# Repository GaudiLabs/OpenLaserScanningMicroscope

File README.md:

## OpenLaserScanningMicroscope 

Open Source Laser Scanning Microscope (OpenLSM)

### Don't click on the files!
Click on the "Download ZIP" Button to the right.
Then unpack the archive.

### Open Source Digital Microfluidics Bio Lab

OpenLSM is an open source design to build a laser scanning microscope from a DVD or Blue-Ray disc reading head. 

For more info on the open source project see:
http://www.gaudi.ch/GaudiLabs/?page_id=652

### License

OpenLSM, all design files and software are licensed under a GNU GENERAL PUBLIC LICENSE
See license file in the repository.

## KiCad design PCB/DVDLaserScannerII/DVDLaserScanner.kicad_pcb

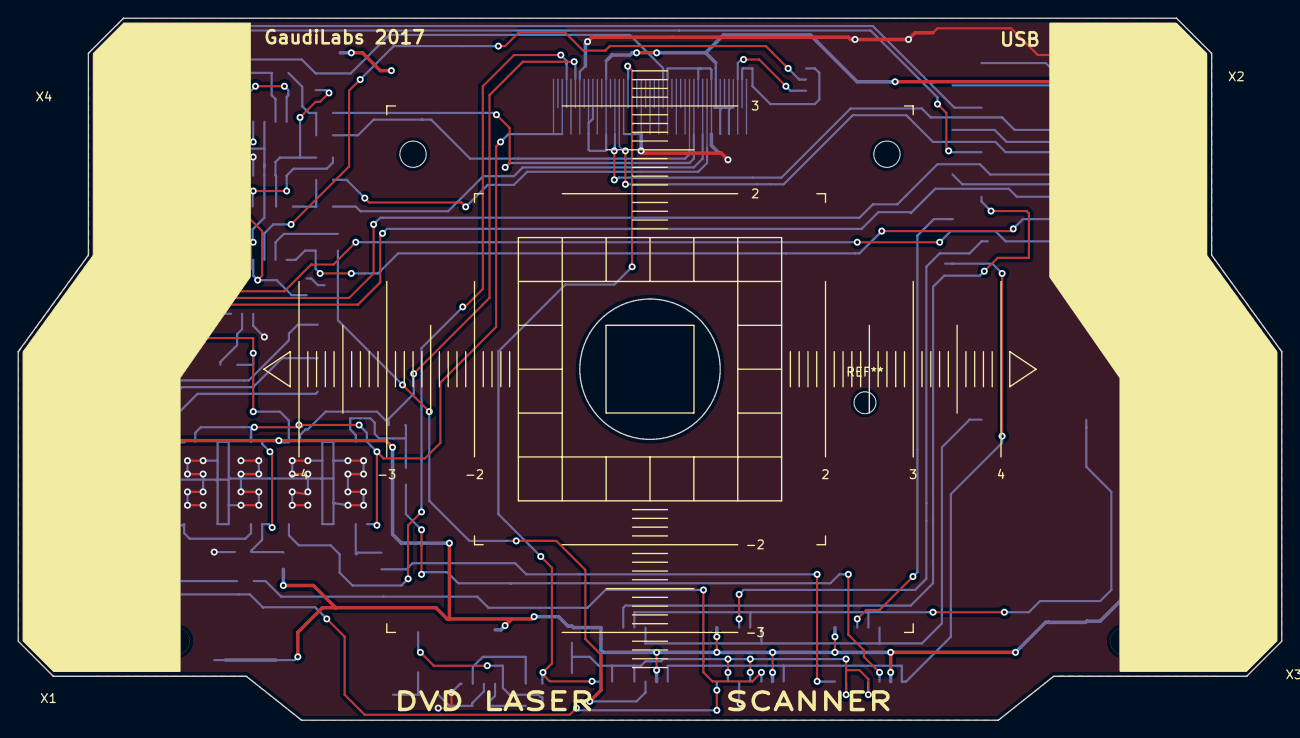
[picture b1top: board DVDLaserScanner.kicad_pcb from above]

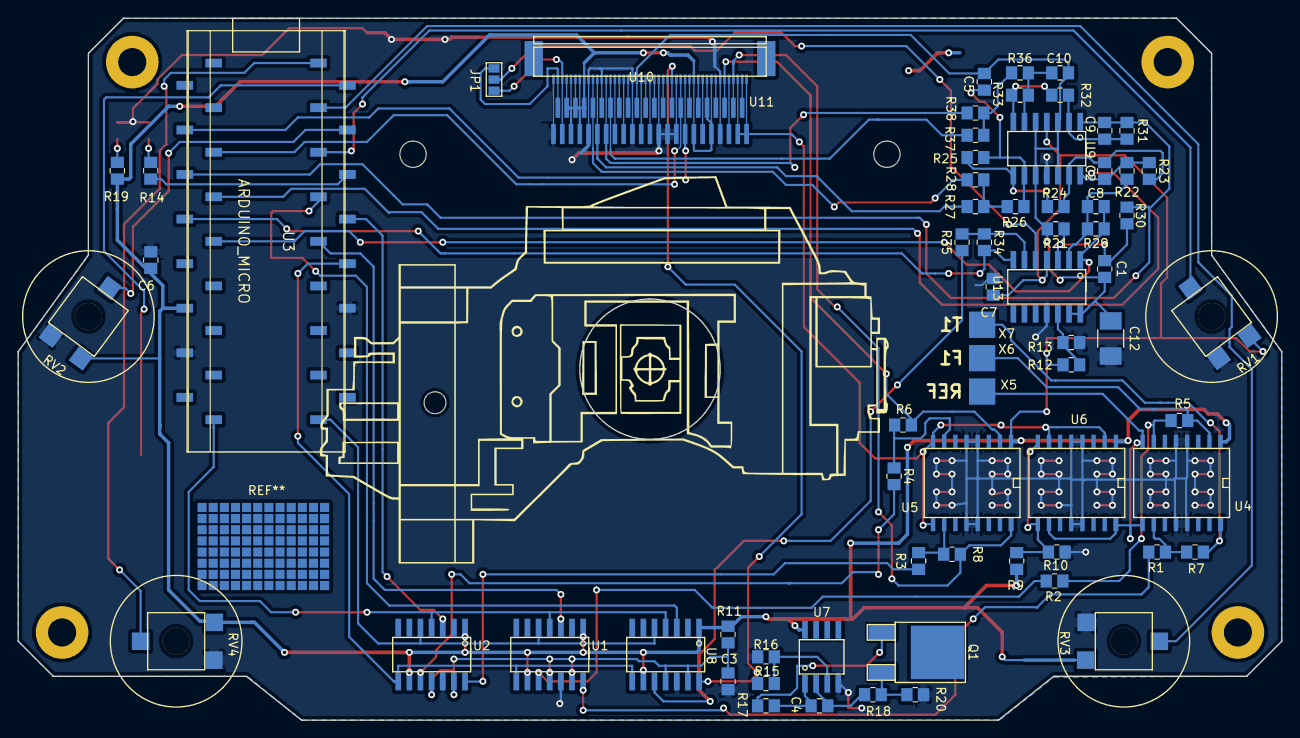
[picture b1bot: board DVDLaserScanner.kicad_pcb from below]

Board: 2 copper layers, 144.0 x 80.0 mm, 77 parts (70 on the bottom side), 80 nets.

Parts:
C1, C8: 22pF; 0805G
C2, C9: 39pF; 0805G
C3: 100nF; 0805G
C4, C6, C7: 100n; 0805G
C5, C10: 10pF; 0805G
C12: 100nF; C_1210_HandSoldering
D1, D2: LED; 0805G
JP1: Jumper_NC_Dual; GS3
Q1: Q_NMOS_GDS; TO-252-2Lead
R1, R3, R5, R6: 15k; 0805G
R2, R4: 270k; 0805G
R7, R8, R15: 8.2k; 0805G
R9, R10, R12: 4.7k; 0805G
R11: 100k; 0805G
R13: 3.3k; 0805G
R14, R19: 470; 0805G
R16: 1.8k; 0805G
R17: 100; 0805G
R18, R22, R30: 10k; 0805G
R20: 10; 0805G
R21, R29: 39k; 0805G
R23, R31: 180k; 0805G
R24, R32: 68k; 0805G
R25, R33: 18k; 0805G
R26, R36: 56k; 0805G
R27, R28, R37, R38: 1.2k; 0805G
R34: 560k; 0805G
R35: 2.7k; 0805G
RV1, RV2, RV3, RV4: POT; CA6_VSMD
SW1: BUT; PUSH_BUTTON_SMD
U1, U2, U8: MCP4922-E/SL; SOIC-14_N
U3: ARDUINO_MICRO; ARDUINO_MICRO_SMD
U4, U5, U6: TCA0372_DWG; SO-16-W
U7: MCP6002; SOIC-08_N
U9, U13: TLC2274; SOIC-14_N
U10: Con45; Pads
U11: Con45; FFC_05_45
X1, X2, X3, X4: MountPad3; MountingHoleM3
X5, X6, X7: PAD; PAD_SMD_3mm

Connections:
A_SIG: R37.1, U10.32, U11.32
B_SIG: R27.1, U10.35, U11.35
C_SIG: R38.1, U10.33, U11.33
DAC1CS: U1.3, U3.9
DAC2CS: U2.3, U3.10
DAC3CS: U3.11, U8.3
DAC_DI: U1.5, U2.5, U3.1, U8.5
DAC_LATCH: U1.8, U2.8, U3.8, U8.8
DAC_SCK: U1.4, U2.4, U3.34, U8.4
D_SIG: R28.1, U10.36, U11.36
F1+: R5.1, U4.2, X6.1
F2+: R8.1, U5.16, U10.4, U11.4
F-: U5.8, U5.9, U6.2, U6.7, U10.1, U10.3, U11.1, U11.3
GND: C3.2, C6.2, C7.2, C12.2, D1.1, D2.1, R10.2, R13.1, R16.2, R20.1, RV1.3, RV2.3, RV3.3, RV4.3, SW1.2, U1.12, U2.12, U3.6, U3.31, U4.4, U4.5, U4.12, U4.13, U5.4, U5.5, U5.12, U5.13, U6.4, U6.5, U6.12, U6.13, U7.4, U8.12, U9.11, U10.7, U10.17, U10.19, U10.21, U10.27, U10.34, U10.37, U10.45, U11.7, U11.17, U11.19, U11.21, U11.27, U11.34, U11.37, U11.45, U13.11
INTENSITY: R15.1, U8.14, U10.18, U11.18
unnamed: C1.2, R21.2, R30.2, U13.3
unnamed: C2.1, R23.1, R24.2, U9.13
unnamed: C4.1, R17.2, U7.1
unnamed: C4.2, R18.2, U7.2
unnamed: C5.1, R25.1, R26.2, U9.9
unnamed: C8.2, R22.2, R29.2, U13.2
unnamed: C9.1, R31.1, R32.2, U9.2
unnamed: C10.1, R33.1, R36.2, U9.6
unnamed: D1.2, R14.2
unnamed: D2.2, R19.2
unnamed: JP1.2, U13.5
unnamed: Q1.1, R17.1
unnamed: Q1.3, R18.1, R20.2
unnamed: R1.1, R7.2, U4.10
unnamed: R1.2, U1.14
unnamed: R2.1, R5.2, U4.7
unnamed: R2.2, U1.10
unnamed: R3.1, R8.2, U5.10
unnamed: R3.2, U2.14
unnamed: R4.1, R6.2, U5.7
unnamed: R4.2, U2.10
unnamed: R9.2, R10.1, U6.8, U6.9
unnamed: R12.1, R13.2, U13.12
unnamed: R14.1, U3.12
unnamed: R15.2, R16.1, U7.3
unnamed: R24.1, R25.2, U9.8
unnamed: R26.1, R27.2, R28.2
unnamed: R32.1, R33.2, U9.7
unnamed: R34.2, R35.1, U13.6
unnamed: R36.1, R37.2, R38.2
unnamed: SW1.1, U3.16
unnamed: U10.2, U11.2
unnamed: U10.5, U11.5
unnamed: U10.8, U11.8
unnamed: U10.11, U11.11
unnamed: U10.12, U11.12
unnamed: U10.14, U11.14
unnamed: U10.20, U11.20
unnamed: U10.22, U11.22
unnamed: U10.23, U11.23
unnamed: U10.24, U11.24
unnamed: U10.25, U11.25
unnamed: U10.28, U11.28
unnamed: U10.29, U11.29
unnamed: U10.30, U11.30
unnamed: U10.31, U11.31
OFFSET: R35.2, U8.10
PD_AC: C9.2, R30.1, R31.2, U3.23, U9.1
PD_BD: C2.2, R22.1, R23.2, U3.24, U9.14
PD_FE: C8.1, R29.1, U3.26, U13.1
PD_RF: R34.1, U3.25, U13.7
POT1: RV1.2, U3.13
POT2: RV2.2, U3.14
POT3: RV3.2, U3.15
POT4: RV4.2, U3.17
RF1: JP1.1, U10.43, U11.43
RF2: JP1.3, U10.44, U11.44
SEL1: U3.22, U10.16, U11.16
SEL2: U3.21, U10.15, U11.15
T1+: R7.1, U4.16, X7.1
T2+: R6.1, U5.2, U10.6, U11.6
VCC_BLUE: C6.1, C7.1, R9.1, R11.1, R12.2, R19.1, RV1.1, RV2.1, RV3.1, RV4.1, U1.1, U1.9, U2.1, U2.9, U3.29, U4.1, U5.1, U6.1, U7.8, U8.1, U8.9, U9.4, U10.9, U10.10, U10.13, U10.38, U10.39, U10.40, U10.41, U10.42, U11.9, U11.10, U11.13, U11.38, U11.39, U11.40, U11.41, U11.42, U13.4
VREF: C1.1, C5.2, C10.2, C12.1, R21.1, U9.3, U9.5, U9.10, U9.12, U10.26, U11.26, U13.13, U13.14
VREF1: U4.8, U4.9, U6.10, U6.16, X5.1
VREF_DAC: C3.1, R11.2, U1.11, U1.13, U2.11, U2.13, U8.11, U8.13

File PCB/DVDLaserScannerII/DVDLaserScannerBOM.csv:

"Id";"Designator";"Package";"Quantity";"Designation";"Supplier and ref";
1;"REF**";"MicroscopeyScale";1;"MicroscopeyScale";;;
2;"U11";"FFC_05_45";1;"Con45";;;
3;"RV4,RV3,RV2,RV1";"CA6_VSMD";4;"POT";;;
4;"U1,U2,U8";"SOIC-14_N";3;"MCP4922-E/SL";;;
5;"U3";"ARDUINO_MICRO_SMD";1;"ARDUINO_MICRO";;;
6;"X1,X2,X3,X4";"MountingHoleM3";4;"MountPad3";;;
7;"C3";"0805G";1;"100nF";;;
8;"R1,R3,R5,R6";"0805G";4;"15k";;;
9;"R2,R4,R26,R36";"0805G";4;"56k";;;
10;"R7,R8,R15";"0805G";3;"8.2k";;;
11;"R9,R10,R12,R34,R35";"0805G";5;"4.7k";;;
12;"R11";"0805G";1;"100k";;;
13;"R13";"0805G";1;"3.3k";;;
14;"C4,C6,C7";"0805G";3;"100n";;;
15;"D1,D2";"0805G";2;"LED";;;
16;"Q1";"TO-252-2Lead";1;"Q_NMOS_GDS";;;
17;"R14,R19";"0805G";2;"470";;;
18;"R16";"0805G";1;"1.8k";;;
19;"R17";"0805G";1;"100";;;
20;"R18,R22,R30";"0805G";3;"10k";;;
21;"R20";"0805G";1;"10";;;
22;"U7";"SOIC-08_N";1;"MCP6002";;;
23;"REF**,REF**";"MountingHole_3mm";2;"MountingHole_3mm";;;
24;"JP1";"GS3";1;"Jumper_NC_Dual";;;
25;"R21,R29";"0805G";2;"39k";;;
26;"U4,U5,U6";"SO-16-W";3;"TCA0372_DWG";;;
27;"U10";"Pads";1;"Con45";;;
28;"SW1";"PUSH_BUTTON_SMD";1;"BUT";;;
29;"C1,C8";"0805G";2;"22pF";;;
30;"C2,C9";"0805G";2;"39pF";;;
31;"C5,C10";"0805G";2;"10pF";;;
32;"R23,R31";"0805G";2;"180k";;;
33;"R24,R32";"0805G";2;"68k";;;
34;"R25,R33";"0805G";2;"18k";;;
35;"R27,R28,R37,R38";"0805G";4;"1.2k";;;
36;"C12";"C_1210_HandSoldering";1;"CP_Small";;;
37;"U9,U13";"SOIC-14_N";2;"TLC2274";;;
38;"G***";"PHR-803T";1;"LOGO";;;
39;"X5,X6,X7";"PAD_SMD_3mm";3;"PAD";;;
40;"REF**";"MountingHole_2-5mm";1;"MountingHole_2-5mm";;;
41;"REF**";"SMD_Array";1;"SMD_Array";;;

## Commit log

2017-10-06 Added PCB files, Arduino and Processing code first online
2020-10-17 Finally fixed error on U9 / U13 and updated BOM
2020-10-17 Updated Schematic PDF
